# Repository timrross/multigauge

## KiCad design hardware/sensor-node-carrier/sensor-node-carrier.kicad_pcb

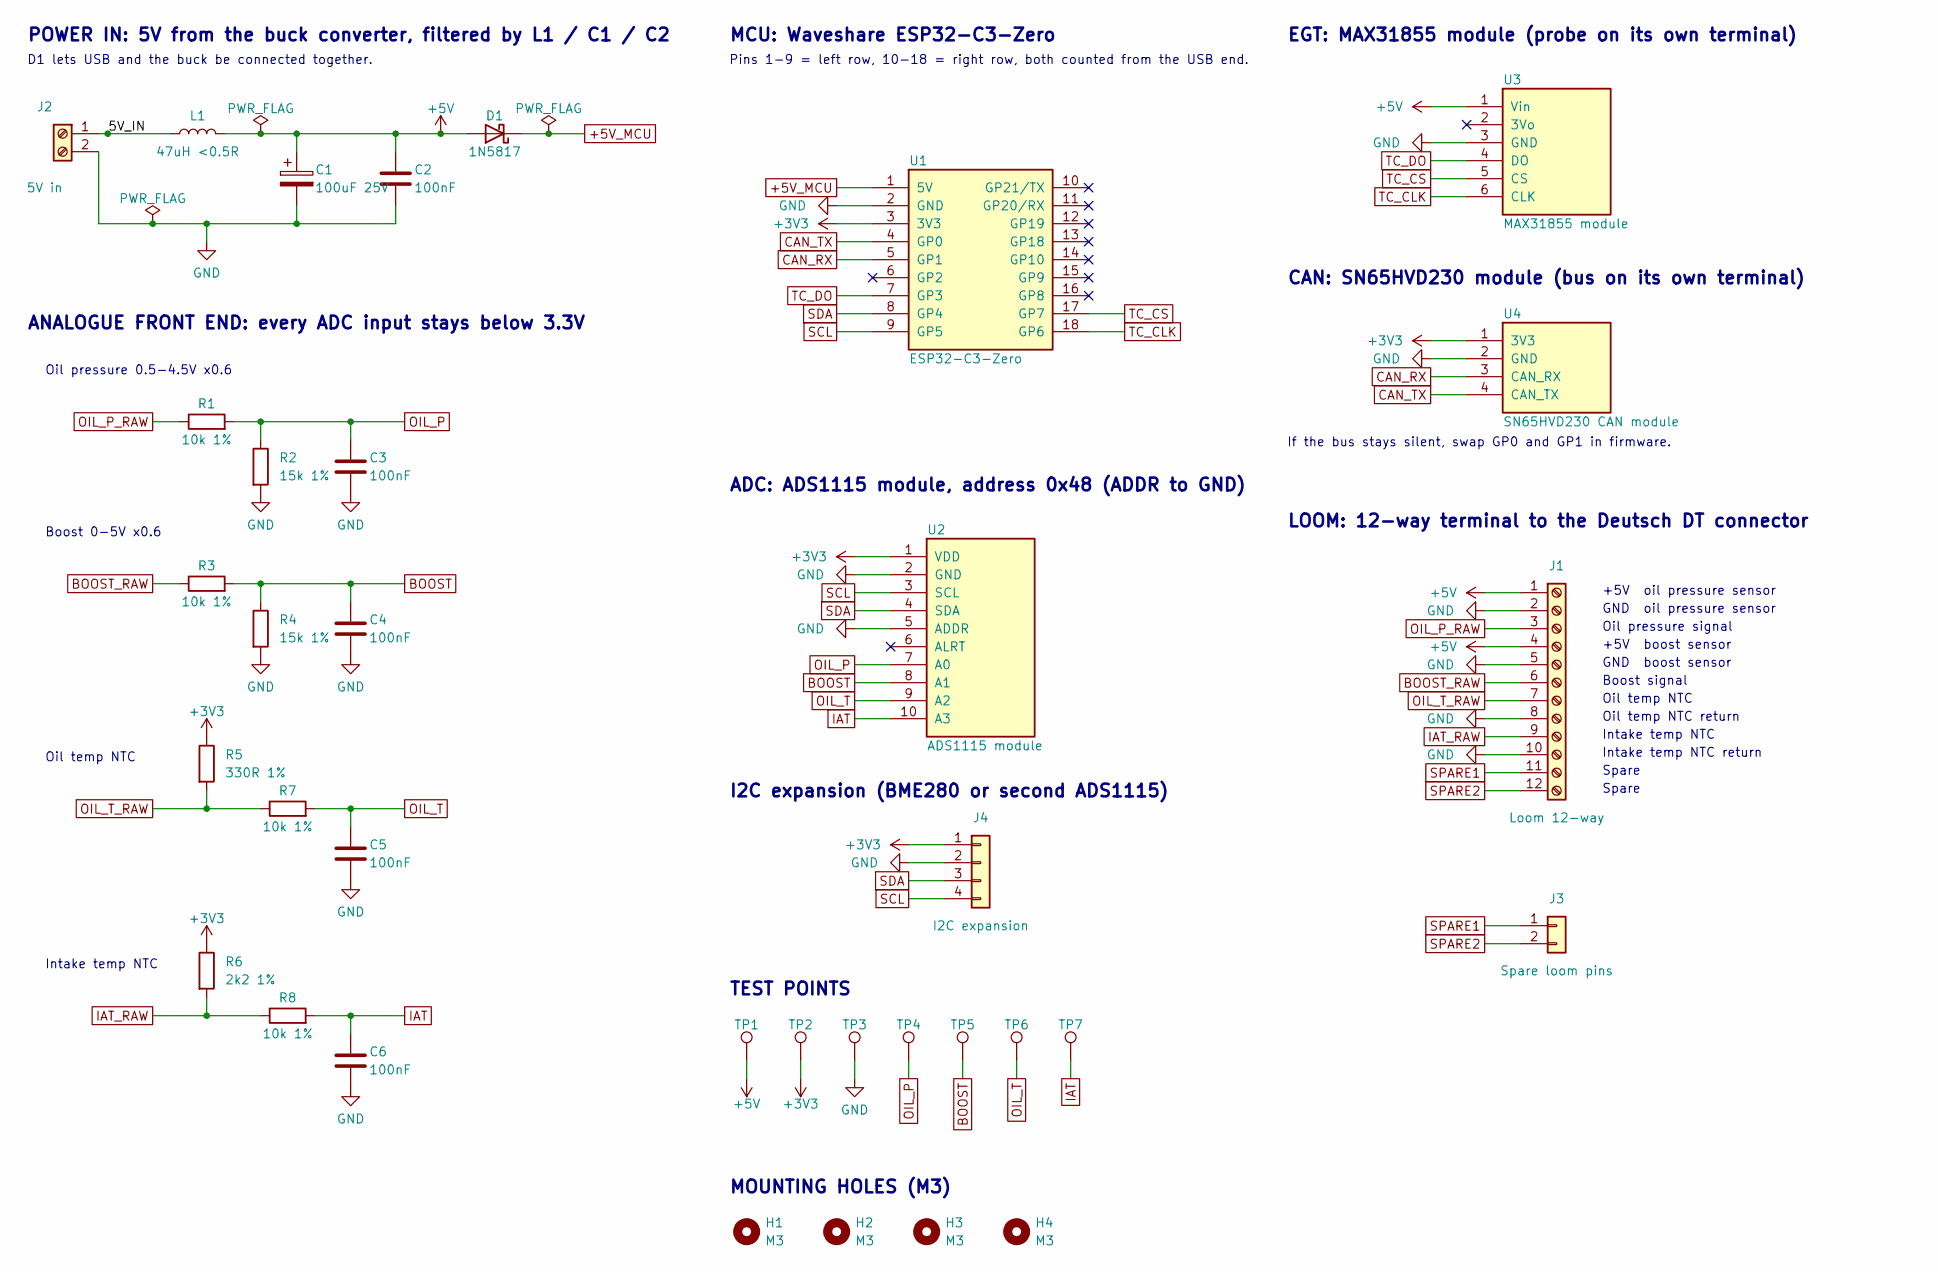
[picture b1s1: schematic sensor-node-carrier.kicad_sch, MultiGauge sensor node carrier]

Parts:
C1: 100uF 25V; CP_Radial_D6.3mm_P2.50mm
C2, C3, C4, C5, C6: 100nF; C_Disc_D5.0mm_W2.5mm_P5.00mm
D1: 1N5817; D_DO-41_SOD81_P10.16mm_Horizontal
H1, H2, H3, H4: M3; MountingHole_3.2mm_M3
J1: Loom 12-way; TerminalBlock_Phoenix_MKDS-1,5-12_1x12_P5.00mm_Horizontal
J2: 5V in; TerminalBlock_Phoenix_MKDS-1,5-2_1x02_P5.00mm_Horizontal
J3: Spare loom pins; PinHeader_1x02_P2.54mm_Vertical
J4: I2C expansion; PinHeader_1x04_P2.54mm_Vertical
L1: 47uH <0.5R; L_Radial_D8.0mm_P5.08mm
R1, R3, R7, R8: 10k 1%; R_Axial_DIN0207_L6.3mm_D2.5mm_P10.16mm_Horizontal
R2, R4: 15k 1%; R_Axial_DIN0207_L6.3mm_D2.5mm_P10.16mm_Horizontal
R5: 330R 1%; R_Axial_DIN0207_L6.3mm_D2.5mm_P10.16mm_Horizontal
R6: 2k2 1%; R_Axial_DIN0207_L6.3mm_D2.5mm_P10.16mm_Horizontal
TP1: +5V; TestPoint_THTPad_D2.0mm_Drill1.0mm
TP2: +3V3; TestPoint_THTPad_D2.0mm_Drill1.0mm
TP3: GND; TestPoint_THTPad_D2.0mm_Drill1.0mm
TP4: OIL_P; TestPoint_THTPad_D2.0mm_Drill1.0mm
TP5: BOOST; TestPoint_THTPad_D2.0mm_Drill1.0mm
TP6: OIL_T; TestPoint_THTPad_D2.0mm_Drill1.0mm
TP7: IAT; TestPoint_THTPad_D2.0mm_Drill1.0mm
U1: ESP32-C3-Zero; Module_Waveshare_ESP32-C3-Zero
U2: ADS1115 module; Module_ADS1115_1x10
U3: MAX31855 module; Module_MAX31855_1x06
U4: SN65HVD230 CAN module; Module_SN65HVD230_1x04

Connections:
+3V3: J4.1, R5.1, R6.1, TP2.1, U1.3 (3V3), U2.1 (VDD), U4.1 (3V3)
+5V: C1.1, C2.1, D1.2 (A), J1.1, J1.4, L1.2, TP1.1, U3.1 (Vin)
+5V_MCU: D1.1 (K), U1.1 (5V)
/5V_IN: J2.1, L1.1
BOOST: C4.1, R3.2, R4.1, TP5.1, U2.8 (A1)
BOOST_RAW: J1.6, R3.1
CAN_RX: U1.5 (GP1), U4.3 (CAN_RX)
CAN_TX: U1.4 (GP0), U4.4 (CAN_TX)
GND: C1.2, C2.2, C3.2, C4.2, C5.2, C6.2, J1.2, J1.5, J1.8, J1.10, J2.2, J4.2, R2.2, R4.2, TP3.1, U1.2 (GND), U2.2 (GND), U2.5 (ADDR), U3.3 (GND), U4.2 (GND)
IAT: C6.1, R8.2, TP7.1, U2.10 (A3)
IAT_RAW: J1.9, R6.2, R8.1
OIL_P: C3.1, R1.2, R2.1, TP4.1, U2.7 (A0)
OIL_P_RAW: J1.3, R1.1
OIL_T: C5.1, R7.2, TP6.1, U2.9 (A2)
OIL_T_RAW: J1.7, R5.2, R7.1
SCL: J4.4, U1.9 (GP5), U2.3 (SCL)
SDA: J4.3, U1.8 (GP4), U2.4 (SDA)
SPARE1: J1.11, J3.1
SPARE2: J1.12, J3.2
TC_CLK: U1.18 (GP6), U3.6 (CLK)
TC_CS: U1.17 (GP7), U3.5 (CS)
TC_DO: U1.7 (GP3), U3.4 (DO)

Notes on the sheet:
If the bus stays silent, swap GP0 and GP1 in firmware.
ANALOGUE FRONT END: every ADC input stays below 3.3V
Boost 0-5V x0.6
CAN: SN65HVD230 module (bus on its own terminal)
Intake temp NTC
Pins 1-9 = left row, 10-18 = right row, both counted from the USB end.
MCU: Waveshare ESP32-C3-Zero
Boost signal
ADC: ADS1115 module, address 0x48 (ADDR to GND)
Oil pressure 0.5-4.5V x0.6
Spare
I2C expansion (BME280 or second ADS1115)
GND boost sensor
Oil temp NTC
EGT: MAX31855 module (probe on its own terminal)
MOUNTING HOLES (M3)
TEST POINTS
+5V oil pressure sensor
Oil pressure signal
Intake temp NTC return
Oil temp NTC return
POWER IN: 5V from the buck converter, filtered by L1 / C1 / C2
GND oil pressure sensor
D1 lets USB and the buck be connected together.
LOOM: 12-way terminal to the Deutsch DT connector
+5V boost sensor

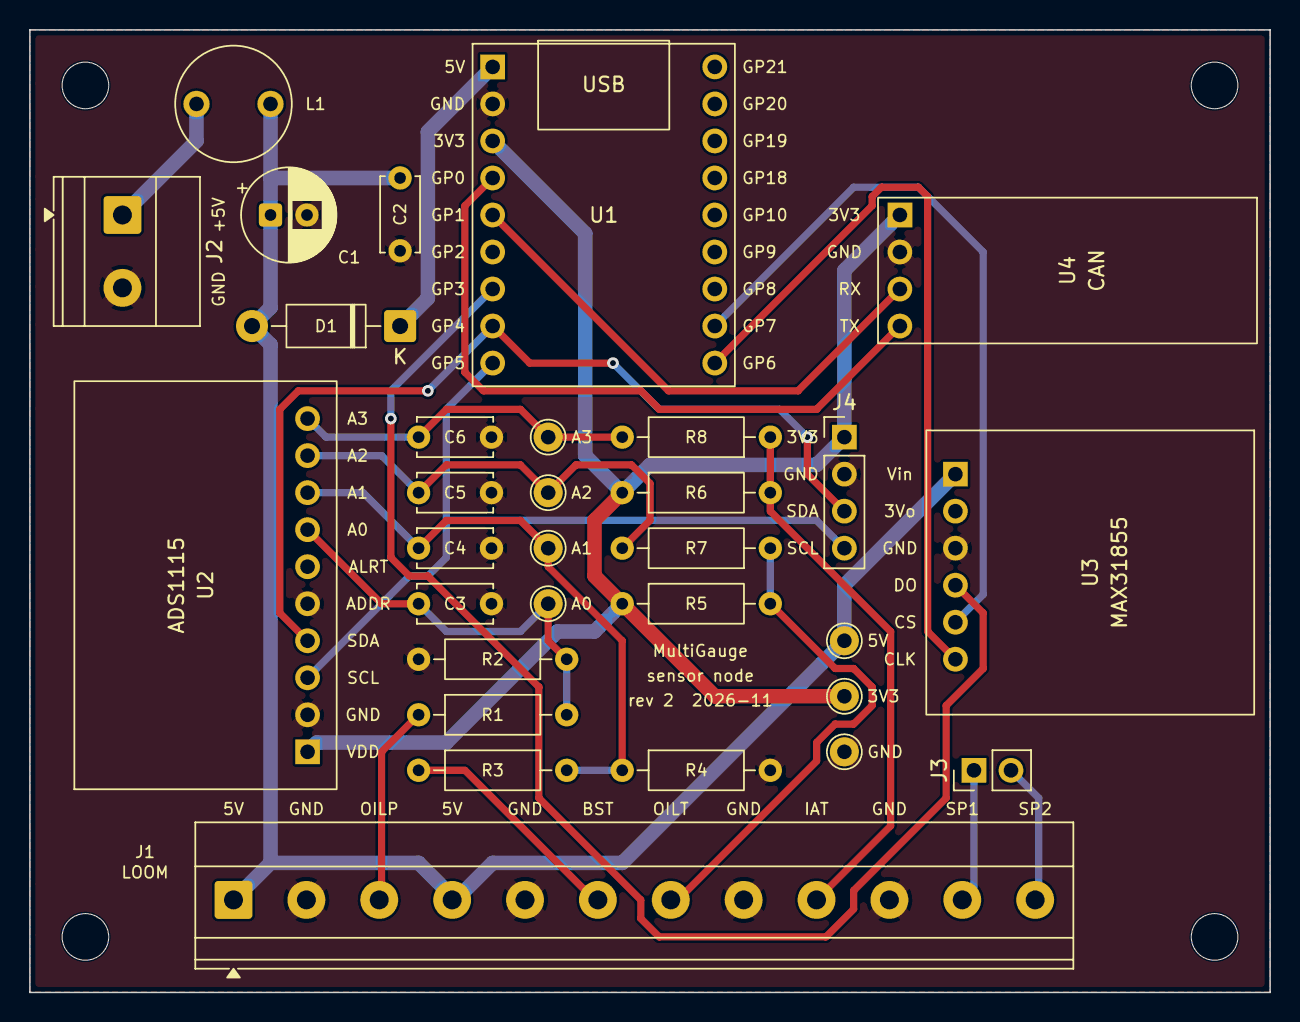
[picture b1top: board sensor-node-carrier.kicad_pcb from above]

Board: 2 copper layers, 85.1 x 66.0 mm, 35 parts (0 on the bottom side), 22 nets.

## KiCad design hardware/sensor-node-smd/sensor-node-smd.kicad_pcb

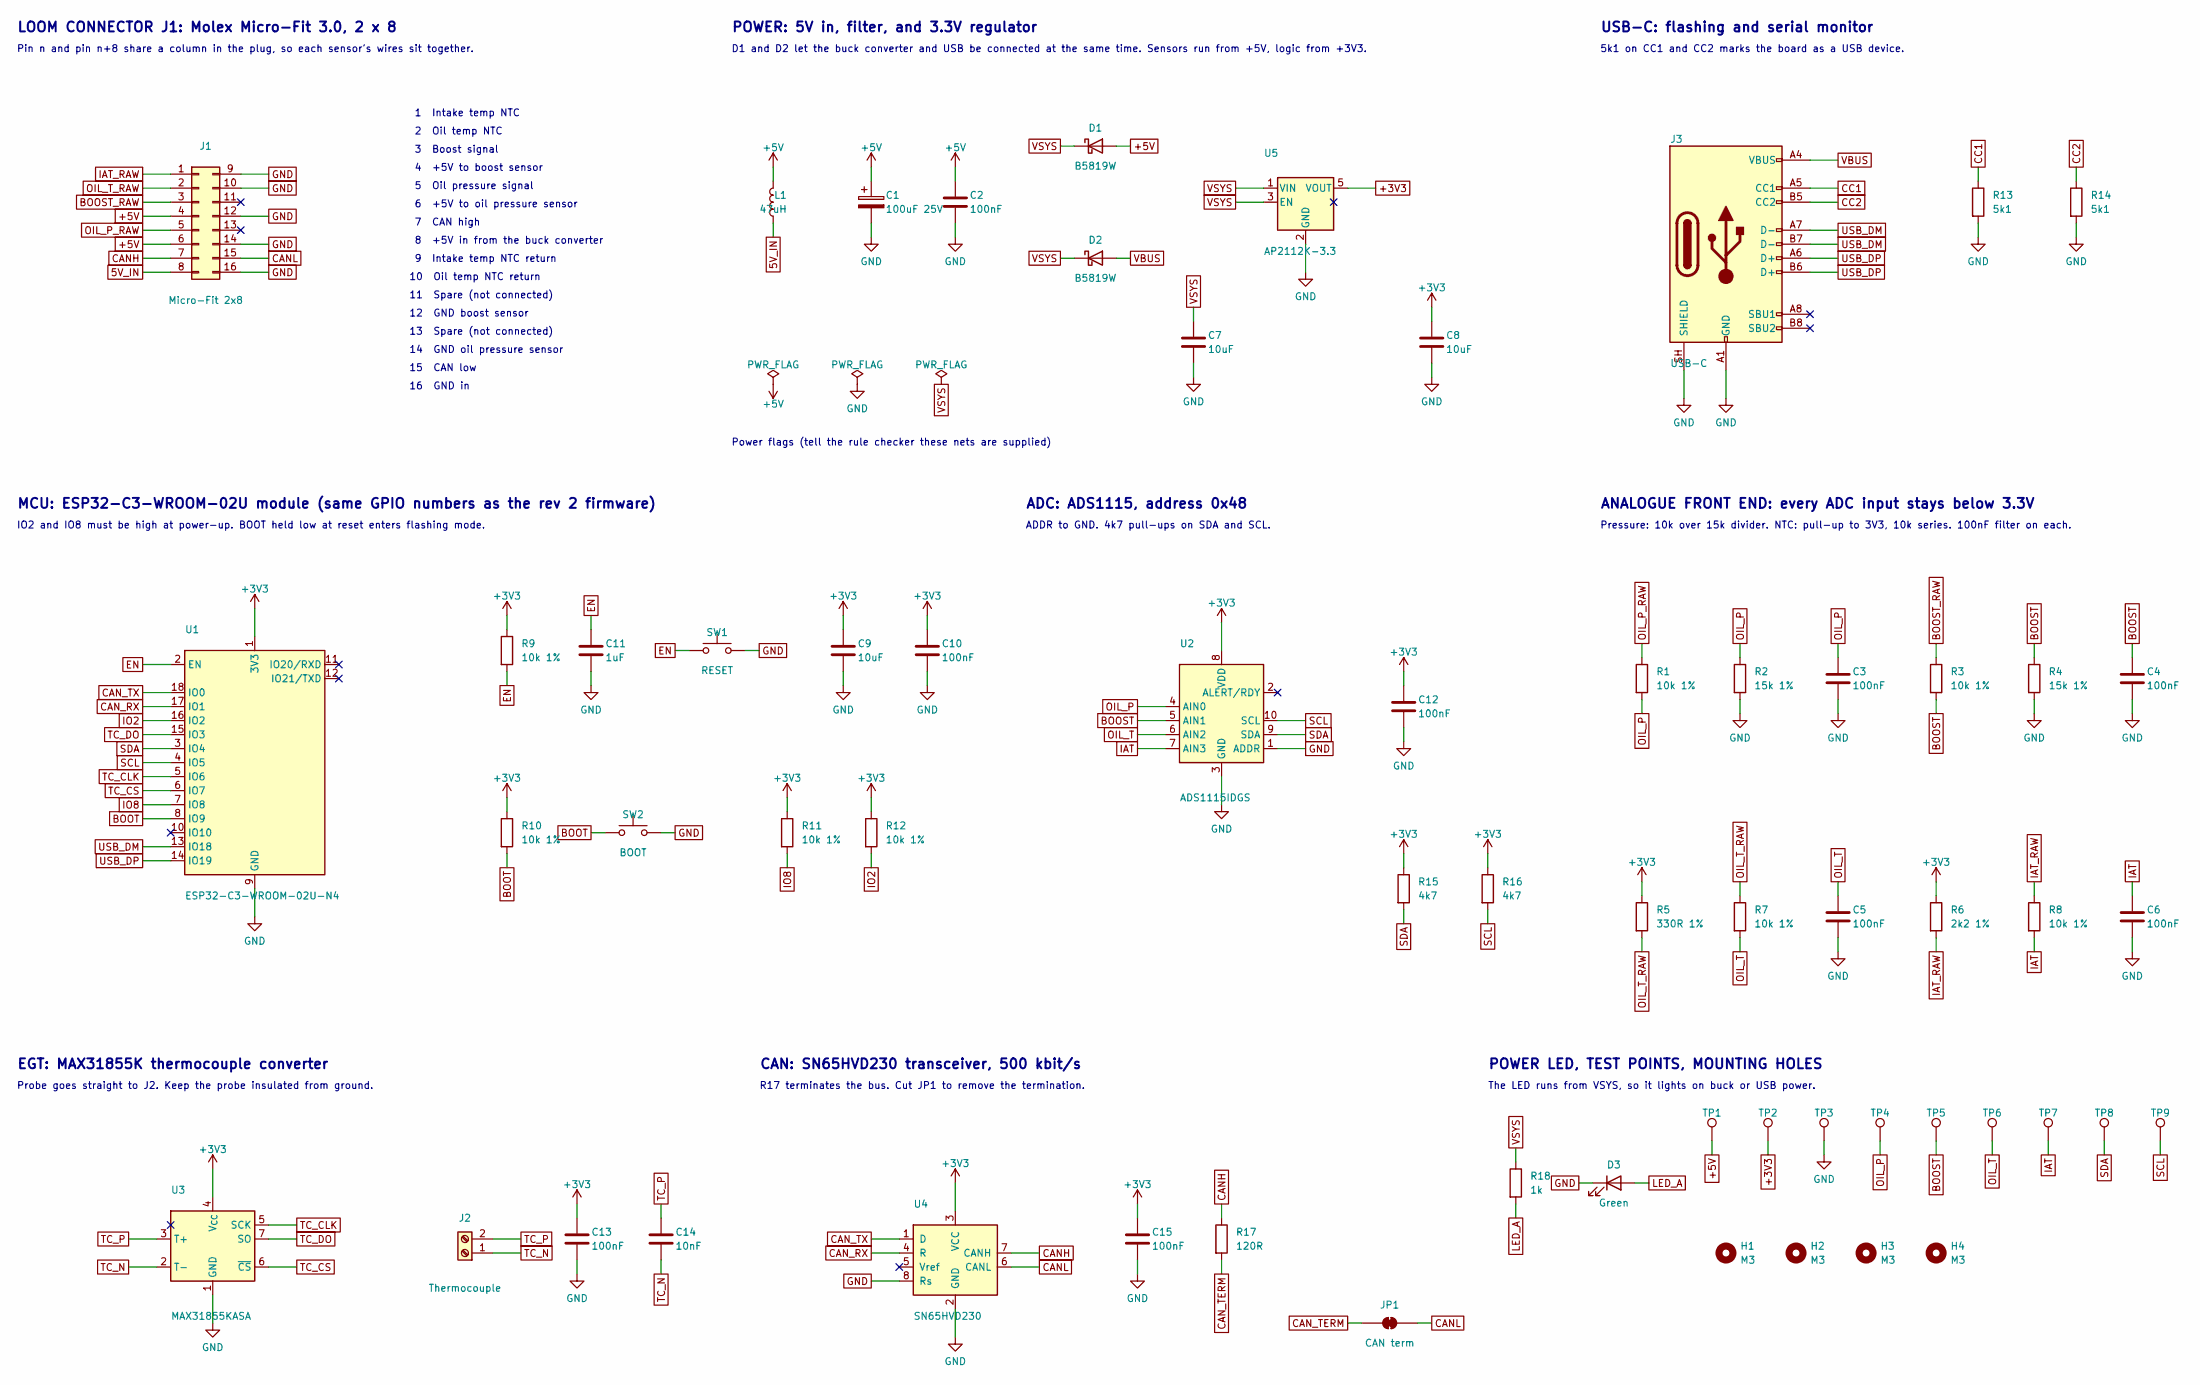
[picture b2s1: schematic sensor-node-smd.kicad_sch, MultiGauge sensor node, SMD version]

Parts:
C1: 100uF 25V; CP_Elec_6.3x7.7; LCSC C3338
C2, C3, C4, C5, C6, C10, C12, C13, C15: 100nF; C_0603_1608Metric; LCSC C14663
C7, C8, C9: 10uF; C_0805_2012Metric; LCSC C15850
C11: 1uF; C_0603_1608Metric; LCSC C15849
C14: 10nF; C_0603_1608Metric; LCSC C57112
D1, D2: B5819W; D_SOD-123; LCSC C8598
D3: Green; LED_0603_1608Metric; LCSC C2986059
H1, H2, H3, H4: M3; MountingHole_3.2mm_M3
J1: Micro-Fit 2x8; Molex_Micro-Fit_3.0_43045-1600_2x08_P3.00mm_Horizontal
J2: Thermocouple; TerminalBlock_Phoenix_MKDS-1,5-2_1x02_P5.00mm_Horizontal
J3: USB-C; USB_C_Receptacle_HRO_TYPE-C-31-M-12; LCSC C165948
JP1: CAN term; SolderJumper-2_P1.3mm_Bridged_RoundedPad1.0x1.5mm
L1: 47uH; L_Changjiang_FNR6045S; LCSC C168087
R1, R3, R7, R8, R9, R10, R11, R12: 10k 1%; R_0603_1608Metric; LCSC C25804
R2, R4: 15k 1%; R_0603_1608Metric; LCSC C22809
R5: 330R 1%; R_0603_1608Metric; LCSC C23138
R6: 2k2 1%; R_0603_1608Metric; LCSC C4190
R13, R14: 5k1; R_0603_1608Metric; LCSC C23186
R15, R16: 4k7; R_0603_1608Metric; LCSC C23162
R17: 120R; R_0603_1608Metric; LCSC C22787
R18: 1k; R_0603_1608Metric; LCSC C21190
SW1: RESET; SW_SPST_B3U-1000P; LCSC C231329
SW2: BOOT; SW_SPST_B3U-1000P; LCSC C231329
TP1: +5V; TestPoint_Pad_D1.0mm
TP2: +3V3; TestPoint_Pad_D1.0mm
TP3: GND; TestPoint_Pad_D1.0mm
TP4: OIL_P; TestPoint_Pad_D1.0mm
TP5: BOOST; TestPoint_Pad_D1.0mm
TP6: OIL_T; TestPoint_Pad_D1.0mm
TP7: IAT; TestPoint_Pad_D1.0mm
TP8: SDA; TestPoint_Pad_D1.0mm
TP9: SCL; TestPoint_Pad_D1.0mm
U1: ESP32-C3-WROOM-02U-N4; ESP32-C3-WROOM-02U_Via0.3mm; LCSC C2926676
U2: ADS1115IDGS; TSSOP-10_3x3mm_P0.5mm; LCSC C37593
U3: MAX31855KASA; SOIC-8_3.9x4.9mm_P1.27mm; LCSC C52028
U4: SN65HVD230; SOIC-8_3.9x4.9mm_P1.27mm; LCSC C12084
U5: AP2112K-3.3; SOT-23-5; LCSC C51118

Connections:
5V_IN: J1.8, L1.1
+3V3: C8.1, C9.1, C10.1, C12.1, C13.1, C15.1, R5.1, R6.1, R9.1, R10.1, R11.1, R12.1, R15.1, R16.1, TP2.1, U1.1 (3V3), U2.8 (VDD), U3.4 (V_{CC}), U4.3 (VCC), U5.5 (VOUT)
+5V: C1.1, C2.1, D1.2 (A), J1.4, J1.6, L1.2, TP1.1
BOOST: C4.1, R3.2, R4.1, TP5.1, U2.5 (AIN1)
BOOST_RAW: J1.3, R3.1
BOOT: R10.2, SW2.1, U1.8 (IO9)
CANH: J1.7, R17.1, U4.7 (CANH)
CANL: J1.15, JP1.2 (B), U4.6 (CANL)
CAN_RX: U1.17 (IO1), U4.4 (R)
CAN_TERM: JP1.1 (A), R17.2
CAN_TX: U1.18 (IO0), U4.1 (D)
CC1: J3.A5 (CC1), R13.1
CC2: J3.B5 (CC2), R14.1
EN: C11.1, R9.2, SW1.1, U1.2 (EN)
GND: C1.2, C2.2, C3.2, C4.2, C5.2, C6.2, C7.2, C8.2, C9.2, C10.2, C11.2, C12.2, C13.2, C15.2, D3.1 (K), J1.9, J1.10, J1.12, J1.14, J1.16, J3.A1 (GND), J3.A12 (GND), J3.B1 (GND), J3.B12 (GND), J3.SH (SHIELD), R2.2, R4.2, R13.2, R14.2, SW1.2, SW2.2, TP3.1, U1.9 (GND), U1.19 (GND), U2.1 (ADDR), U2.3 (GND), U3.1 (GND), U4.2 (GND), U4.8 (Rs), U5.2 (GND)
IAT: C6.1, R8.2, TP7.1, U2.7 (AIN3)
IAT_RAW: J1.1, R6.2, R8.1
IO2: R12.2, U1.16 (IO2)
IO8: R11.2, U1.7 (IO8)
LED_A: D3.2 (A), R18.2
OIL_P: C3.1, R1.2, R2.1, TP4.1, U2.4 (AIN0)
OIL_P_RAW: J1.5, R1.1
OIL_T: C5.1, R7.2, TP6.1, U2.6 (AIN2)
OIL_T_RAW: J1.2, R5.2, R7.1
SCL: R16.2, TP9.1, U1.4 (IO5), U2.10 (SCL)
SDA: R15.2, TP8.1, U1.3 (IO4), U2.9 (SDA)
TC_CLK: U1.5 (IO6), U3.5 (SCK)
TC_CS: U1.6 (IO7), U3.6 (~CS)
TC_DO: U1.15 (IO3), U3.7 (SO)
TC_N: C14.2, J2.1, U3.2 (T-)
TC_P: C14.1, J2.2, U3.3 (T+)
USB_DM: J3.A7 (D-), J3.B7 (D-), U1.13 (IO18)
USB_DP: J3.A6 (D+), J3.B6 (D+), U1.14 (IO19)
VBUS: D2.2 (A), J3.A4 (VBUS), J3.A9 (VBUS), J3.B4 (VBUS), J3.B9 (VBUS)
VSYS: C7.1, D1.1 (K), D2.1 (K), R18.1, U5.1 (VIN), U5.3 (EN)

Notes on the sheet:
POWER LED, TEST POINTS, MOUNTING HOLES
5 Oil pressure signal
Pressure: 10k over 15k divider. NTC: pull-up to 3V3, 10k series. 100nF filter on each.
Pin n and pin n+8 share a column in the plug, so each sensor's wires sit together.
EGT: MAX31855K thermocouple converter
CAN: SN65HVD230 transceiver, 500 kbit/s
R17 terminates the bus. Cut JP1 to remove the termination.
16 GND in
6 +5V to oil pressure sensor
IO2 and IO8 must be high at power-up. BOOT held low at reset enters flashing mode.
ADDR to GND. 4k7 pull-ups on SDA and SCL.
D1 and D2 let the buck converter and USB be connected at the same time. Sensors run from +5V, logic from +3V3.
9 Intake temp NTC return
ADC: ADS1115, address 0x48
13 Spare (not connected)
POWER: 5V in, filter, and 3.3V regulator
2 Oil temp NTC
Probe goes straight to J2. Keep the probe insulated from ground.
8 +5V in from the buck converter
USB-C: flashing and serial monitor
The LED runs from VSYS, so it lights on buck or USB power.
12 GND boost sensor
10 Oil temp NTC return
ANALOGUE FRONT END: every ADC input stays below 3.3V
5k1 on CC1 and CC2 marks the board as a USB device.
1 Intake temp NTC
MCU: ESP32-C3-WROOM-02U module (same GPIO numbers as the rev 2 firmware)
4 +5V to boost sensor
14 GND oil pressure sensor
11 Spare (not connected)
LOOM CONNECTOR J1: Molex Micro-Fit 3.0, 2 x 8
3 Boost signal
7 CAN high
Power flags (tell the rule checker these nets are supplied)
15 CAN low

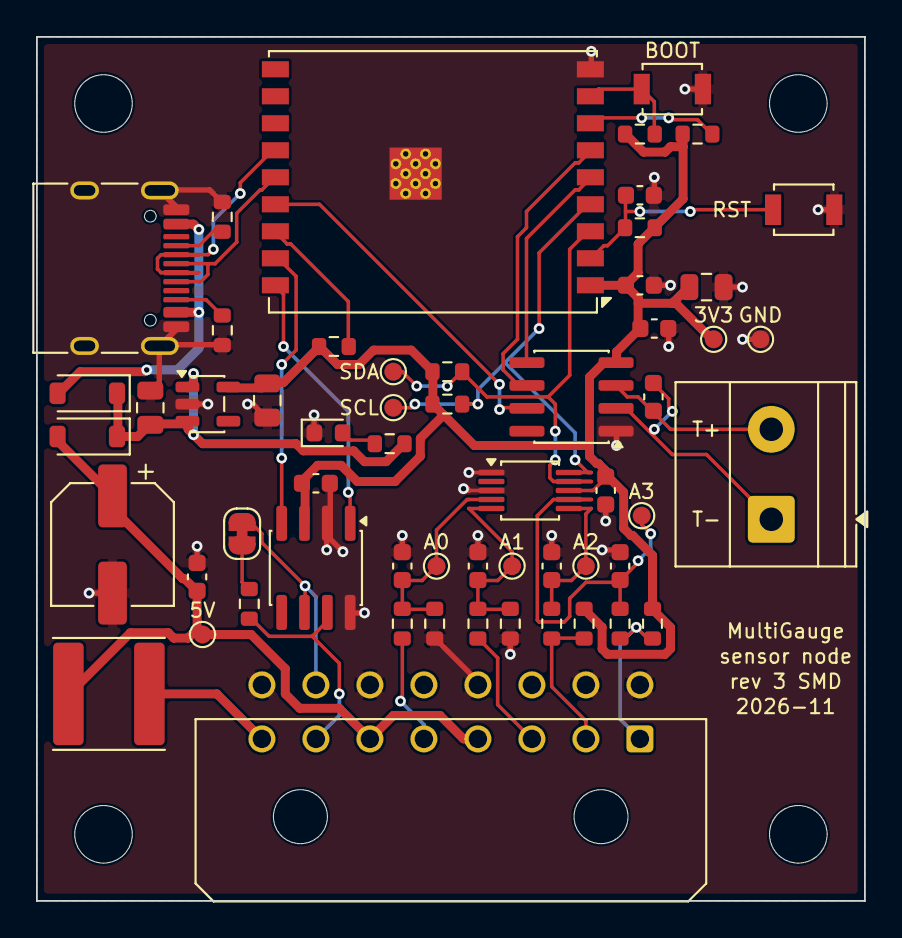
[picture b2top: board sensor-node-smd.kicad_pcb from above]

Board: 2 copper layers, 46.0 x 48.0 mm, 61 parts (0 on the bottom side), 35 nets.

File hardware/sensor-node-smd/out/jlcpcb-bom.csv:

Comment,Designator,Footprint,LCSC Part #
100uF 25V,C1,CP_Elec_6.3x7.7,C3338
100nF,"C2,C3,C4,C5,C6,C10,C12,C13,C15",C_0603_1608Metric,C14663
10uF,"C7,C8,C9",C_0805_2012Metric,C15850
1uF,C11,C_0603_1608Metric,C15849
10nF,C14,C_0603_1608Metric,C57112
B5819W,"D1,D2",D_SOD-123,C8598
Green,D3,LED_0603_1608Metric,C2986059
USB-C,J3,USB_C_Receptacle_HRO_TYPE-C-31-M-12,C165948
47uH,L1,L_Changjiang_FNR6045S,C168087
10k 1%,"R1,R3,R7,R8,R9,R10,R11,R12",R_0603_1608Metric,C25804
15k 1%,"R2,R4",R_0603_1608Metric,C22809
330R 1%,R5,R_0603_1608Metric,C23138
2k2 1%,R6,R_0603_1608Metric,C4190
5k1,"R13,R14",R_0603_1608Metric,C23186
4k7,"R15,R16",R_0603_1608Metric,C23162
120R,R17,R_0603_1608Metric,C22787
1k,R18,R_0603_1608Metric,C21190
RESET,SW1,SW_SPST_B3U-1000P,C231329
BOOT,SW2,SW_SPST_B3U-1000P,C231329
ESP32-C3-WROOM-02U-N4,U1,ESP32-C3-WROOM-02U_Via0.3mm,C2926676
ADS1115IDGS,U2,TSSOP-10_3x3mm_P0.5mm,C37593
MAX31855KASA,U3,SOIC-8_3.9x4.9mm_P1.27mm,C52028
SN65HVD230,U4,SOIC-8_3.9x4.9mm_P1.27mm,C12084
AP2112K-3.3,U5,SOT-23-5,C51118

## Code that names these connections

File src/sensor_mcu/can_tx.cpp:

#include <Arduino.h>
#include <driver/twai.h>
#include "can_tx.h"
#include "can_protocol.h"
#include "sensor.h"

// Heartbeat counter
static uint8_t heartbeatCounter = 0;

bool initCAN() {
  // Configure TWAI (CAN) peripheral
  twai_general_config_t g_config = TWAI_GENERAL_CONFIG_DEFAULT(
    (gpio_num_t)CAN_TX_PIN,
    (gpio_num_t)CAN_RX_PIN,
    TWAI_MODE_NORMAL
  );

  // 500 kbit/s timing
  twai_timing_config_t t_config = TWAI_TIMING_CONFIG_500KBITS();

  // No acceptance filter - accept all messages
  twai_filter_config_t f_config = TWAI_FILTER_CONFIG_ACCEPT_ALL();

  // Install TWAI driver
  if (twai_driver_install(&g_config, &t_config, &f_config) != ESP_OK) {
    return false;
  }

  // Start TWAI driver
  if (twai_start() != ESP_OK) {
    return false;
  }

  return true;
}

static uint32_t txFailCount = 0;

// Helper to transmit a CAN message
static bool transmitMessage(uint32_t id, const void* data, uint8_t len) {
  // Zero-initialize to ensure ss/self/dlc_non_comp flag bits are not garbage.
  // Uninitialized flags can set self-reception mode (loopback), causing the
  // RX queue to fill with our own frames.
  twai_message_t message = {};
  message.identifier = id;
  message.extd = 0;  // Standard 11-bit ID
  message.rtr = 0;   // Not a remote frame
  message.data_length_code = len;
  memcpy(message.data, data, len);

  // Queue message for transmission (10ms timeout). This fails when the queue
  // is full (nothing on the bus is acknowledging) or the driver is not running.
  if (twai_transmit(&message, pdMS_TO_TICKS(10)) != ESP_OK) {
    txFailCount++;
    return false;
  }
  return true;
}

uint32_t canTxFailCount() {
  return txFailCount;
}

void maintainCAN() {
  // With no other node on the bus, frames are never acknowledged. That alone only
  // takes the controller to error-passive (it keeps retrying and the TX queue fills).
  // Real bus faults (shorted or swapped wires, wrong bitrate) take it to BUS_OFF.
  //
  // Recovery is two steps: twai_initiate_recovery() runs the 128 x 11 recessive bit
  // sequence and then leaves the driver STOPPED, so it must be started again.
  static twai_state_t lastState = TWAI_STATE_RUNNING;
  twai_status_info_t status;
  if (twai_get_status_info(&status) != ESP_OK) return;

  if (status.state != lastState) {
    static const char* const names[] = { "STOPPED", "RUNNING", "BUS_OFF", "RECOVERING" };
    Serial.printf("[CAN] state %s (tx errors %lu, rx errors %lu, tx failed %lu)\n",
                  status.state <= TWAI_STATE_RECOVERING ? names[status.state] : "?",
                  (unsigned long)status.tx_error_counter, (unsigned long)status.rx_error_counter,
                  (unsigned long)txFailCount);
    lastState = status.state;
  }

  if (status.state == TWAI_STATE_BUS_OFF) {
    twai_initiate_recovery();
  } else if (status.state == TWAI_STATE_STOPPED) {
    twai_start();
  }
}

void sendBoostMessage(const Reading& boost) {
  CanMsgBoost msg = {};
  encodeBoostMsg(&msg, boost.value, boost.fault);
  transmitMessage(CAN_ID_BOOST, &msg, sizeof(msg));
}

void sendOilMessage(const Reading& temp, const Reading& pressure) {
  CanMsgOil msg = {};
  encodeOilMsg(&msg, temp.value, temp.fault, pressure.value, pressure.fault);
  transmitMessage(CAN_ID_OIL, &msg, sizeof(msg));
}

void sendEgtMessage(const Reading& egt) {
  CanMsgEgt msg = {};
  encodeEgtMsg(&msg, egt.value, egt.fault);
  transmitMessage(CAN_ID_EGT, &msg, sizeof(msg));
}

void sendIntercoolerMessage(const Reading& temp) {
  CanMsgIntercooler msg = {};
  encodeIntercoolerMsg(&msg, temp.value, temp.fault);
  transmitMessage(CAN_ID_INTERCOOLER, &msg, sizeof(msg));
}

void sendHeartbeat(uint8_t faultFlags) {
  CanMsgHeartbeat msg = {};
  encodeHeartbeatMsg(&msg, heartbeatCounter++, millis(), faultFlags);
  transmitMessage(CAN_ID_HEARTBEAT, &msg, sizeof(msg));
}
